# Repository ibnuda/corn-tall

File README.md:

# Corn Tall

ehehehe.

## Screenshots

Front view.

Back view.

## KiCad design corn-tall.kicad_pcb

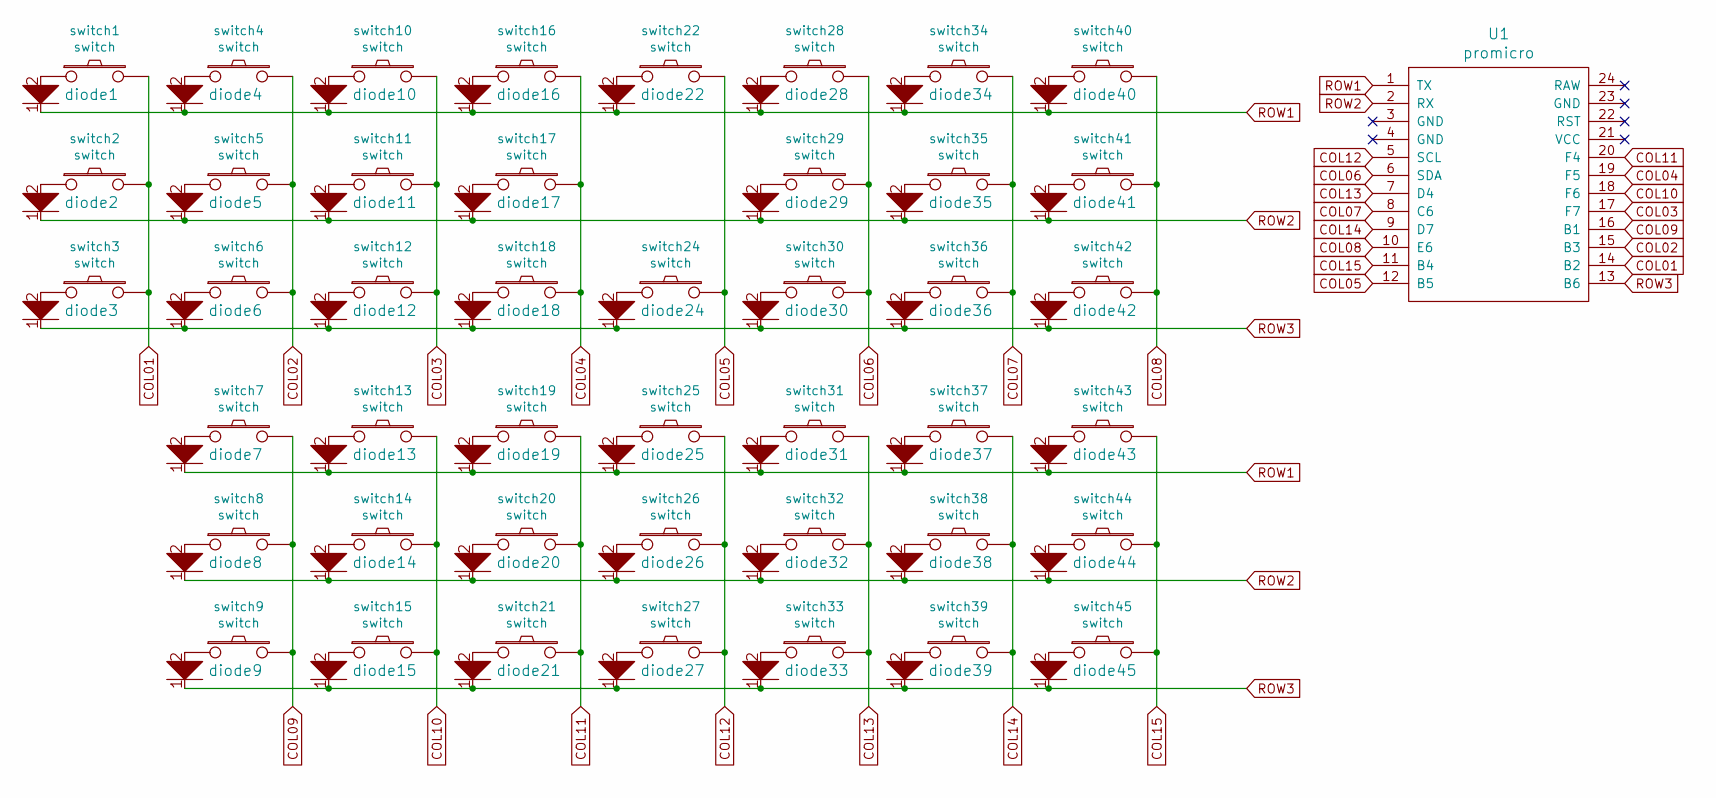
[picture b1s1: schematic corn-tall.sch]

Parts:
U1: promicro
diode1, diode2, diode3, diode4, diode5, diode6, diode7, diode8, diode9, diode10, diode11, diode12, diode13, diode14, diode15, diode16, diode17, diode18, diode19, diode20, diode21, diode22, diode24, diode25, diode26, diode27, diode28, diode29, diode30, diode31, diode32, diode33, diode34, diode35, diode36, diode37, diode38, diode39, diode40, diode41, diode42, diode43, diode44, diode45: diode
switch1, switch2, switch3, switch4, switch5, switch6, switch7, switch8, switch9, switch10, switch11, switch12, switch13, switch14, switch15, switch16, switch17, switch18, switch19, switch20, switch21, switch22, switch24, switch25, switch26, switch27, switch28, switch29, switch30, switch31, switch32, switch33, switch34, switch35, switch36, switch37, switch38, switch39, switch40, switch41, switch42, switch43, switch44, switch45: switch; 1u-single

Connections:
COL01: U1.14 (B2), switch1.2, switch2.2, switch3.2
COL02: U1.15 (B3), switch4.2, switch5.2, switch6.2
COL03: U1.17 (F7), switch10.2, switch11.2, switch12.2
COL04: U1.19 (F5), switch16.2, switch17.2, switch18.2
COL05: U1.12 (B5), switch22.2, switch24.2
COL06: U1.6 (SDA), switch28.2, switch29.2, switch30.2
COL07: U1.8 (C6), switch34.2, switch35.2, switch36.2
COL08: U1.10 (E6), switch40.2, switch41.2, switch42.2
COL09: U1.16 (B1), switch7.2, switch8.2, switch9.2
COL10: U1.18 (F6), switch13.2, switch14.2, switch15.2
COL11: U1.20 (F4), switch19.2, switch20.2, switch21.2
COL12: U1.5 (SCL), switch25.2, switch26.2, switch27.2
COL13: U1.7 (D4), switch31.2, switch32.2, switch33.2
COL14: U1.9 (D7), switch37.2, switch38.2, switch39.2
COL15: U1.11 (B4), switch43.2, switch44.2, switch45.2
unnamed: diode1.2, switch1.1
unnamed: diode2.2, switch2.1
unnamed: diode3.2, switch3.1
unnamed: diode4.2, switch4.1
unnamed: diode5.2, switch5.1
unnamed: diode6.2, switch6.1
unnamed: diode7.2, switch7.1
unnamed: diode8.2, switch8.1
unnamed: diode9.2, switch9.1
unnamed: diode10.2, switch10.1
unnamed: diode11.2, switch11.1
unnamed: diode12.2, switch12.1
unnamed: diode13.2, switch13.1
unnamed: diode14.2, switch14.1
unnamed: diode15.2, switch15.1
unnamed: diode16.2, switch16.1
unnamed: diode17.2, switch17.1
unnamed: diode18.2, switch18.1
unnamed: diode19.2, switch19.1
unnamed: diode20.2, switch20.1
unnamed: diode21.2, switch21.1
unnamed: diode22.2, switch22.1
unnamed: diode24.2, switch24.1
unnamed: diode25.2, switch25.1
unnamed: diode26.2, switch26.1
unnamed: diode27.2, switch27.1
unnamed: diode28.2, switch28.1
unnamed: diode29.2, switch29.1
unnamed: diode30.2, switch30.1
unnamed: diode31.2, switch31.1
unnamed: diode32.2, switch32.1
unnamed: diode33.2, switch33.1
unnamed: diode34.2, switch34.1
unnamed: diode35.2, switch35.1
unnamed: diode36.2, switch36.1
unnamed: diode37.2, switch37.1
unnamed: diode38.2, switch38.1
unnamed: diode39.2, switch39.1
unnamed: diode40.2, switch40.1
unnamed: diode41.2, switch41.1
unnamed: diode42.2, switch42.1
unnamed: diode43.2, switch43.1
unnamed: diode44.2, switch44.1
unnamed: diode45.2, switch45.1
ROW1: U1.1 (TX), diode1.1, diode4.1, diode7.1, diode10.1, diode13.1, diode16.1, diode19.1, diode22.1, diode25.1, diode28.1, diode31.1, diode34.1, diode37.1, diode40.1, diode43.1
ROW2: U1.2 (RX), diode2.1, diode5.1, diode8.1, diode11.1, diode14.1, diode17.1, diode20.1, diode26.1, diode29.1, diode32.1, diode35.1, diode38.1, diode41.1, diode44.1
ROW3: U1.13 (B6), diode3.1, diode6.1, diode9.1, diode12.1, diode15.1, diode18.1, diode21.1, diode24.1, diode27.1, diode30.1, diode33.1, diode36.1, diode39.1, diode42.1, diode45.1

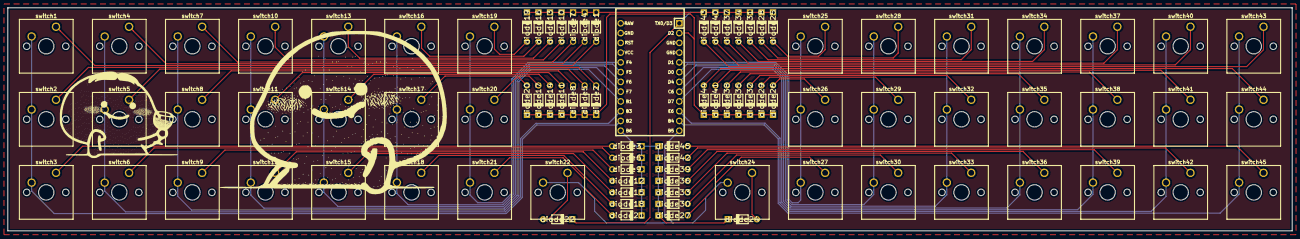
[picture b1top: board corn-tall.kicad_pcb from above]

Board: 2 copper layers, 334.0 x 58.0 mm, 89 parts (1 on the bottom side), 62 nets.

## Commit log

2020-08-04 init commit
2020-08-04 fill-in zones.
2020-08-04 readme
